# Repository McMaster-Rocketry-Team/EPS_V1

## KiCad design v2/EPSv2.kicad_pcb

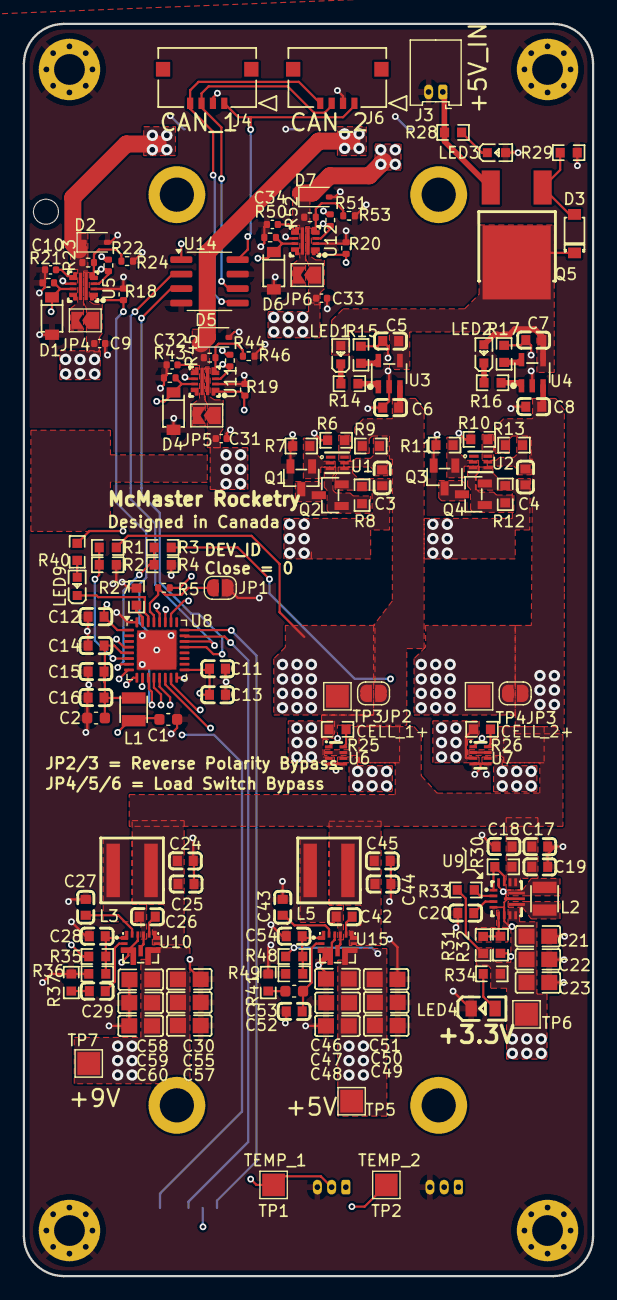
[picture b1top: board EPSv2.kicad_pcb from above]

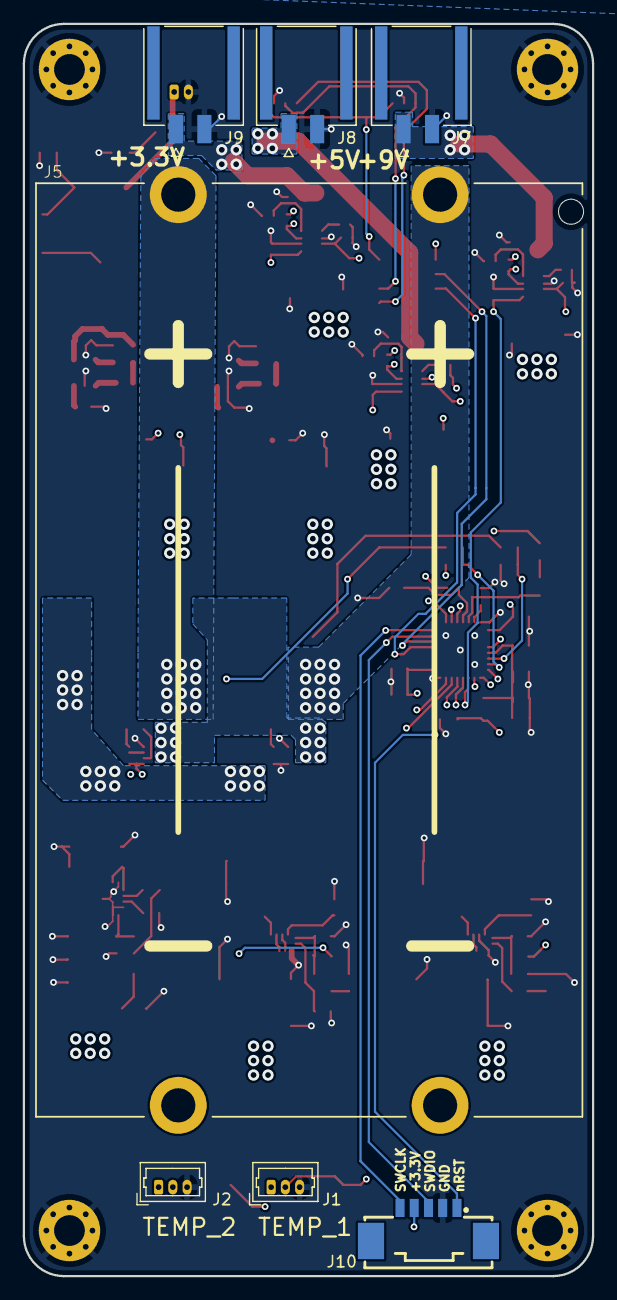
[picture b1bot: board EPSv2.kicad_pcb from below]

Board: 4 copper layers, 50.0 x 110.0 mm, 163 parts (7 on the bottom side), 85 nets.

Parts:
C1, C2: 47uF; C_0603_1608Metric
C3, C4, C12, C13, C15, C20: 100nF 0603; C0603
C5, C6, C7, C8, C11, C16: 4.7uF 0603; C0603
C9, C31, C33: 1u / 20V; C_0402_1005Metric
C10, C32, C34: 5n; C_0402_1005Metric
C14: 10nF 0603; C0603
C17, C18, C19: 10uF 0603; C0603
C21, C22, C23: 22uF 0805; C0805
C24, C45: CL10A106KP8NNNC (10uF 0603); C0603
C25, C26, C42, C44: CC0603KRX7R9BB104 (100nF 0603); C0603
C27, C43: CL10A225KO8NNNC; C0603
C28, C54: CL10C270JB8NNNC; C0603
C29: CC0603KRX7R9BB203; C0603
C30, C46, C47, C48, C49, C50, C51, C55, C57, C58, C59, C60: CL21A226MAQNNNE (22uF 0805); C0805
C52: CL10C220JB8NNNC; C0603
C53: 33nF; C_0603_1608Metric
D1, D4, D6: DDZ9678-7; SOD-123_L2.7-W1.6-LS3.7-RD
D2, D5, D7: 1N5819WS; D_SOD-323
D3: BZT52C11-7-F; SOD-123_L2.8-W1.8-LS3.7-RD
H1, H2, H3, H4: MountingHole_Pad; MountingHole_2.7mm_M2.5_Pad_Via
J1, J2: Conn_01x03; Molex_PicoBlade_53047-0310_1x03_P1.25mm_Vertical
J3: Conn_01x02; Molex_PicoBlade_53048-0210_1x02_P1.25mm_Horizontal
J4, J6: 5037630491; CON_5037630491
J5: 2P 21700 Cell Holder; PA21700x2-THM_Parallel
J7, J8, J9: 1053091102; 1054301102
J10: Conn_01x05_Pin; CONN-SMD_5P-P1.25_532610571-2
JP1, JP2, JP3: SolderJumper_2_Open; SolderJumper-2_P1.3mm_Open_RoundedPad1.0x1.5mm
JP4, JP5, JP6: SolderJumper_2_Open; SolderJumper-2_P1.3mm_Open_TrianglePad1.0x1.5mm
L1, L2: 1.5uF 2.9A; IND-SMD_L2.5-W2.0_MEKK2520TR47M
L3, L5: SRP5030CA-2R2M; IND-SMD_L5.5-W5.3
LED1, LED2, LED9: Yellow; LED0603-RD-YELLOW
LED3: KT-0603R (RED); LED0603-RD
LED4: 0805G (Green); LED0805-R-RD
Q1, Q2, Q3, Q4: AO3400A; SOT-23-3_L2.9-W1.3-P1.90-LS2.4-BR
Q5: AP25P06K; TO-252-2_L6.6-W6.1-P4.57-LS10.1-BL
R1, R2, R3, R4, R31: 470k 0603; R0603
R5: 10k; R_0402_1005Metric
R6, R10: 2.2k 0603; R0603
R7, R8, R11, R12: 2M 0603; R0603
R9, R13: 330R 0603; R0603
R14, R16, R28, R40: 0603WAF1001T5E (1k 0603); R0603
R15, R17: 2k 0603; R0603
R18, R19, R20: 470k; R_0402_1005Metric
R21, R22, R43, R44, R50, R51: 1k; R_0402_1005Metric
R23, R45, R52: 47k; R_0402_1005Metric
R24, R46, R53: 33k; R_0402_1005Metric
R25, R26, R33: 100k 0603; R0603
R27: 5.1k 0603; R0603
R29, R49: 0603WAF1003T5E (100k 0603); R0603
R30: 10k 0603; R0603
R32: 150k 0603; R0603
R34: 1k 0603; R0603
R35: FRC0603F1432TS; R0603
R36: 0603WAF2003T5E; R0603
R37: FRC0603F1872TS; R0603
R41: FRC0603F5761TS; R0603
R48: 0603WAF1372T5E; R0603
TP1, TP2, TP3, TP4, TP5, TP6, TP7: TestPoint; TestPoint_Pad_2.0x2.0mm
U1, U2: BQ29700DSER; WSON-6_L1.5-W1.5-P0.50-TL
U3, U4: MCP73831T-2ACI/OT; SOT-23-5_L3.0-W1.7-P0.95-LS2.8-BL
U5, U11, U12: LM73100RPWR; VQFN-10_L2.0-W2.0-P0.45-TL
U6, U7: C3235556 (M66200DRLR); SOT-583-8_L2.1-W1.2-P0.50-LS1.6-BL
U8: STM32L432KCUx; QFN-32-1EP_5x5mm_P0.5mm_EP3.45x3.45mm
U9: TPS63070RNMR; VQFN-HR-15_L3.0-W2.5-P0.50-BL_TPS63070RNMR
U10, U15: TPS61288LRQQR; VQFN-HR-11_L3.0-W2.5-P0.50-TL
U14: ISO1044BD; SOIC-8_3.9x4.9mm_P1.27mm

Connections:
+3.3V: C1.1, C11.2, C12.2, C13.2, C21.2, C22.2, C23.2, C33.1, J1.1, J2.1, J10.4, JP6.1 (A), L1.1, R5.1, R22.1, R31.2, R33.2, R34.2, R40.2, R44.1, R51.1, TP6.1, U8.1 (VDD), U8.17 (VDD), U9.7 (Vout), U9.8 (Vout), U12.5 (IN)
+3.3V_PG: R51.2, U8.26 (PB3), U12.3 (PG)
+5V: C31.1, C46.2, C47.2, C48.2, C49.2, C50.2, C51.2, JP5.1 (A), R48.2, TP5.1, U11.5 (IN), U15.5 (VOUT)
+5V_PG: R44.2, U8.27 (PB4), U11.3 (PG)
+9V: C9.1, C30.2, C55.2, C57.2, C58.2, C59.2, C60.2, JP4.1 (A), R35.2, TP7.1, U5.5 (IN), U10.5 (VOUT)
+9V_PG: R22.2, U5.3 (PG), U8.28 (PB5)
/DEV_ID: JP1.1 (A), R5.2, U8.29 (PB6)
/LM7310_3.3V/VOUT: D7.1 (K), J9.1, JP6.2 (B), R52.1, U12.6 (OUT)
/LM7310_5V/VOUT: D5.1 (K), J8.1, JP5.2 (B), R45.1, U11.6 (OUT)
/LM7310_9V/VOUT: D2.1 (K), J7.1, JP4.2 (B), R23.1, U5.6 (OUT)
/LM66200_2/VOUT: C17.2, C18.2, C19.2, C24.2, C25.2, C44.2, C45.2, L3.1, L5.1, R30.2, U6.2 (VOUT), U6.7 (VOUT), U7.2 (VOUT), U7.7 (VOUT), U9.12 (Vin), U9.13 (Vin), U10.6 (EN), U10.7 (VIN), U15.6 (EN), U15.7 (VIN)
/MCP73831_1/+5V_VIN: C5.2, C7.2, D3.1 (K), LED1.2 (A), LED2.2 (A), Q5.3 (D), U3.4 (VDD), U4.4 (VDD)
/Reverse_Polarity/VIN: J3.1, Q5.2 (S), R28.2
/STM32L432KCUx/+3V3A: C2.1, C14.2, C15.2, C16.2, L1.2, U8.5 (VDDA)
/STM32L432KCUx/PB7: LED9.1 (C), U8.30 (PB7)
/STM32L432KCUx/SWDCLK: J10.5, U8.24 (PA14)
/STM32L432KCUx/SWDIO: J10.3, U8.23 (PA13)
/STM32L432KCUx/nRST: J10.1, U8.4 (NRST)
CAN_RX: U8.21 (PA11), U14.3 (RXD)
CAN_TX: U8.22 (PA12), U14.2 (TXD)
CELL_1+: C6.2, J5.4, JP2.1 (A), JP2.2 (B), R1.2, R9.2, R25.2, R26.2, TP3.1, U3.3 (VBAT), U6.3 (VIN1), U7.3 (VIN1)
CELL_1-: C3.1, J5.3, Q2.2 (S), R8.1, U1.4 (VSS)
CELL_1_VMON: R1.1, R2.2, U8.6 (PA0)
CELL_2+: C8.2, J5.1, JP3.1 (A), JP3.2 (B), R3.2, R13.2, TP4.1, U4.3 (VBAT), U6.6 (VIN2), U7.6 (VIN2)
CELL_2-: C4.1, J5.2, Q4.2 (S), R12.1, U2.4 (VSS)
CELL_2_VMON: R3.1, R4.2, U8.7 (PA1)
GND: C1.2, C2.2, C5.1, C6.1, C7.1, C8.1, C9.2, C10.2, C11.1, C12.1, C13.1, C14.1, C15.1, C16.1, C17.1, C18.1, C19.1, C20.1, C21.1, C22.1, C23.1, C24.1, C25.1, C27.1, C28.1, C30.1, C31.2, C32.2, C33.2, C34.2, C43.1, C44.1, C45.1, C46.1, C47.1, C48.1, C49.1, C50.1, C51.1, C52.1, C54.1, C55.1, C57.1, C58.1, C59.1, C60.1, D1.2 (A), D2.2 (A), D4.2 (A), D5.2 (A), D6.2 (A), D7.2 (A), H1.1, H2.1, H3.1, H4.1, J1.3, J2.3, J3.2, J4.2 (GND), J6.2 (GND), J7.2, J8.2, J9.2, J10.2, JP1.2 (B), LED3.2 (A), LED4.2 (K), Q1.2 (S), Q3.2 (S), R2.1, R4.1, R6.1, R7.1, R10.1, R11.1, R15.1, R17.1, R18.2, R19.2, R20.2, R21.2, R24.2, R27.1, R29.1, R32.1, R36.1, R37.1, R41.1, R43.2, R46.2, R49.1, R50.2, R53.2, U3.2 (VSS), U4.2 (VSS), U5.2 (OVLO), U5.8 (GND), U6.1 (GND), U6.4 (~ON), U6.5 (GND), U7.1 (GND), U7.4 (~ON), U7.5 (GND), U8.16 (VSS), U8.32 (VSS), U8.33 (VSS), U9.4 (GND), U9.6 (FB2), U9.10 (PGND), U9.15 (Vsel), U10.3 (PGND), U10.10 (AGND), U11.2 (OVLO), U11.8 (GND), U12.2 (OVLO), U12.8 (GND), U14.4 (GND1), U14.7 (GND2), U15.3 (PGND), U15.10 (AGND)
LM7310_IOUT_1: D1.1 (C), R21.1, U5.9 (IMON), U8.8 (PA2)
LM7310_IOUT_2: D4.1 (C), R43.1, U8.9 (PA3), U11.9 (IMON)
LM7310_IOUT_3: D6.1 (C), R50.1, U8.10 (PA4), U12.9 (IMON)
unnamed: C26.2, L3.2, U10.4 (SW), U10.9 (SW)
unnamed: C29.1, R37.2
unnamed: C42.2, L5.2, U15.4 (SW), U15.9 (SW)
unnamed: C53.2, R41.2
unnamed: D3.2 (A), Q5.1 (G), R29.2
unnamed: J4.3 (CANH), J6.3 (CANH), U14.6 (CANH)
unnamed: J4.4 (CANL), J6.4 (CANL), U14.5 (CANL)
unnamed: J4.1 (VCC), J6.1 (VCC), U14.1 (VCC1), U14.8 (VCC2)
unnamed: LED1.1 (C), R14.1
unnamed: LED2.1 (C), R16.1
unnamed: LED3.1 (K), R28.1
unnamed: LED4.1 (A), R34.1
unnamed: LED9.2 (A), R40.1
unnamed: Q1.3 (D), Q2.3 (D)
unnamed: Q1.1 (G), R7.2, U1.2 (COUT)
unnamed: Q2.1 (G), R8.2, U1.3 (DOUT)
unnamed: Q3.3 (D), Q4.3 (D)
unnamed: Q3.1 (G), R11.2, U2.2 (COUT)
unnamed: Q4.1 (G), R12.2, U2.3 (DOUT)
unnamed: C3.2, R9.1, U1.5 (BAT)
unnamed: R6.2, U1.6 (V-)
unnamed: C4.2, R13.1, U2.5 (BAT)
unnamed: R10.2, U2.6 (V-)
unnamed: R15.2, U3.5 (PROG)
unnamed: R14.2, U3.1 (STAT)
unnamed: R17.2, U4.5 (PROG)
unnamed: R16.2, U4.1 (STAT)
unnamed: C10.1, U5.7 (DVDT)
unnamed: R23.2, R24.1, U5.4 (PGTH)
unnamed: R25.1, U6.8 (ST)
unnamed: R26.1, U7.8 (ST)
unnamed: R27.2, U8.31 (PH3)
unnamed: R30.1, U9.1 (PS/SYNC), U9.14 (EN)
unnamed: R31.1, R32.2, U9.5 (FB)
unnamed: L2.1, U9.11 (L1)
unnamed: L2.2, U9.9 (L2)
unnamed: R33.1, U9.2 (PG)
unnamed: C20.2, U9.3 (Vaux)
unnamed: C26.1, U10.8 (BST)
unnamed: C29.2, U10.2 (COMP)
unnamed: C28.2, R35.1, R36.2, U10.1 (FB)
unnamed: C27.2, U10.11 (VCC)
unnamed: C32.1, U11.7 (DVDT)
unnamed: R45.2, R46.1, U11.4 (PGTH)
unnamed: C34.1, U12.7 (DVDT)
unnamed: R52.2, R53.1, U12.4 (PGTH)
unnamed: C42.1, U15.8 (BST)
unnamed: C52.2, C53.1, U15.2 (COMP)
unnamed: C54.2, R48.1, R49.2, U15.1 (FB)
unnamed: C43.2, U15.11 (VCC)
TEMP_1: J1.2, TP1.1, U8.14 (PB0)
TEMP_2: J2.2, TP2.1, U8.15 (PB1)
~MCU_LS_1: R18.1, U5.1 (EN/UVLO), U8.11 (PA5)
~MCU_LS_2: R19.1, U8.12 (PA6), U11.1 (EN/UVLO)
~MCU_LS_3: R20.1, U8.13 (PA7), U12.1 (EN/UVLO)

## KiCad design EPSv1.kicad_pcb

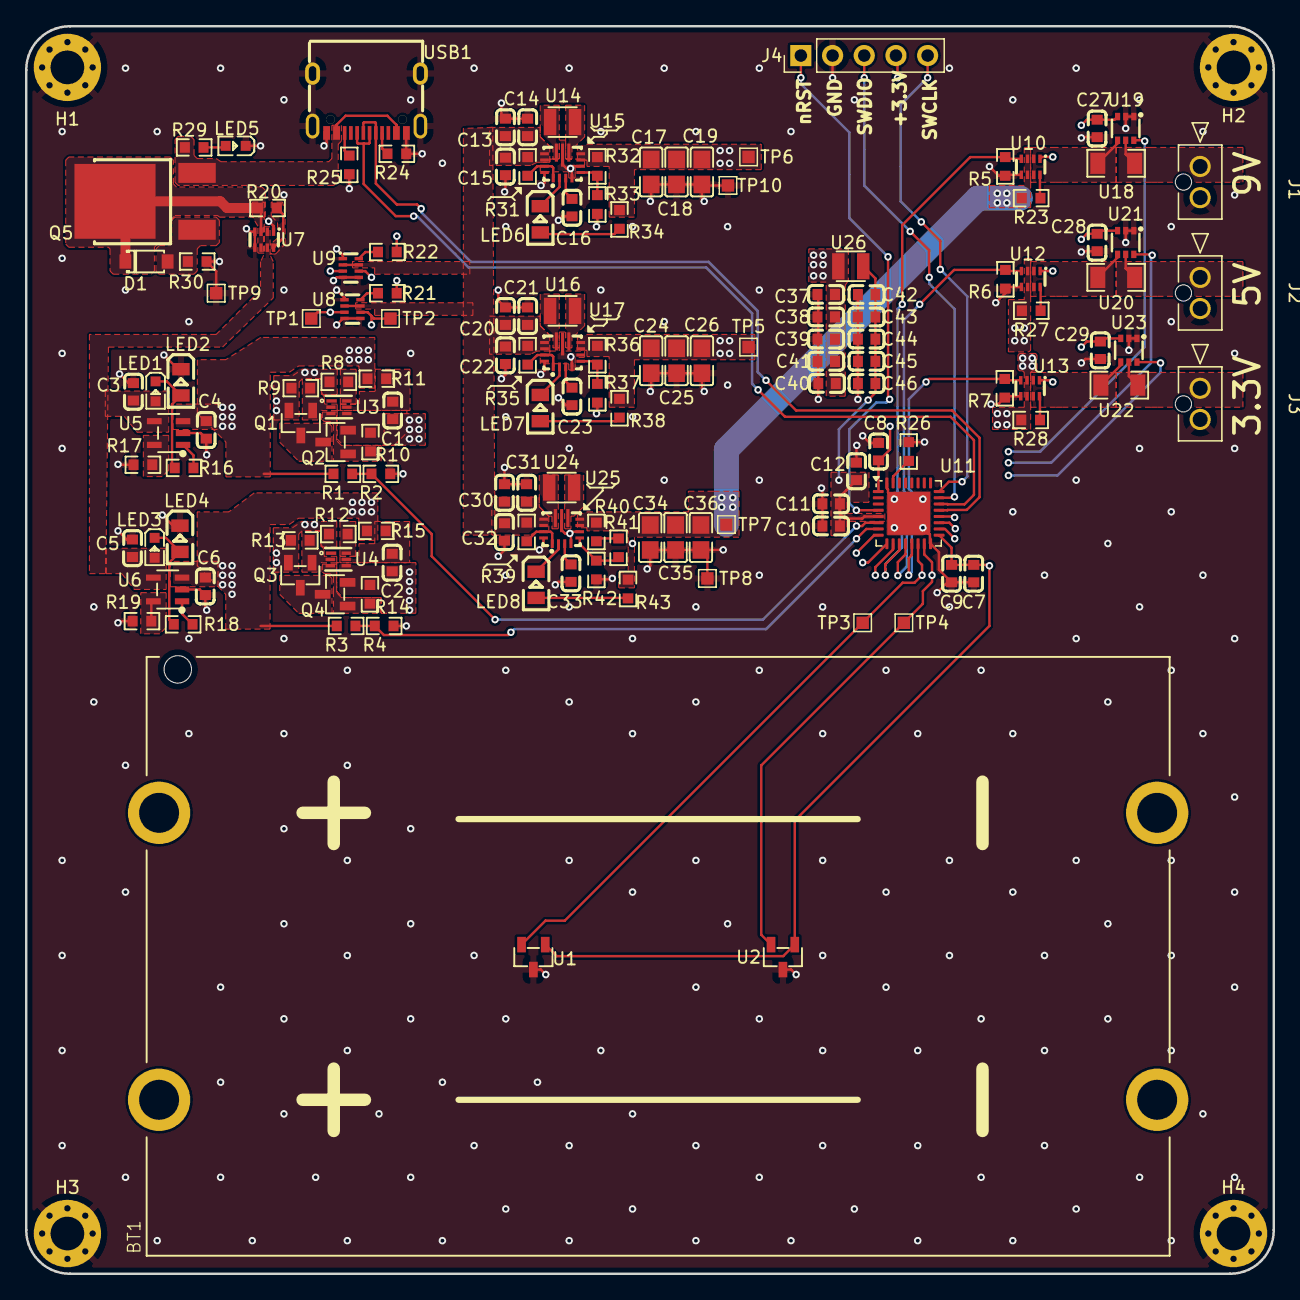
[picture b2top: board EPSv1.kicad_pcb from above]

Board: 4 copper layers, 100.0 x 100.0 mm, 149 parts (0 on the bottom side), 83 nets.

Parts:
BT1: 2P 21700 Cell Holder; PA21700x2-THM_Parallel
C1, C2, C8, C9, C11, C16, C23, C27, C28, C29, C33: 100nF 0603; C0603
C3, C4, C5, C6, C7, C12: 4.7uF 0603; C0603
C10: 10nF 0603; C0603
C13, C14, C15, C20, C21, C22, C30, C31, C32, C37, C38, C39, C40, C41, C42, C43, C44, C45, C46: 10uF 0603; C0603
C17, C18, C19, C24, C25, C26, C34, C35, C36: 22uF 0805; C0805
D1: BZT52C11-7-F; SOD-123_L2.8-W1.8-LS3.7-RD
H1, H2, H3, H4: MountingHole_Pad; MountingHole_2.7mm_M2.5_Pad_Via
J1, J2, J3: 1053091102; CON_1053091102
J4: Conn_01x05_Pin; PinHeader_1x05_P2.54mm_Vertical
LED1, LED3: Yellow; LED0603-RD-YELLOW
LED2, LED4: Green; LED0805-R-RD
LED5: KT-0603R (RED); LED0603-RD
LED6, LED7, LED8: 0805G (Green); LED0805-R-RD
Q1, Q2, Q3, Q4: AO3400A; SOT-23-3_L2.9-W1.3-P1.90-LS2.4-BR
Q5: AP25P06K; TO-252-2_L6.6-W6.1-P4.57-LS10.1-BL
R1, R2, R3, R4, R32: 470k 0603; R0603
R5, R6, R7, R20, R21, R22, R23, R27, R28: 100k 0603; R0603
R8, R12: 2.2k 0603; R0603
R9, R10, R13, R14: 2M 0603; R0603
R11, R15, R16, R18, R34, R38, R43: 330R 0603; R0603
R17, R19: 2k 0603; R0603
R24, R25, R26: 5.1k 0603; R0603
R29: 0603WAF1001T5E (1k 0603); R0603
R30: 0603WAF1003T5E (100k 0603); R0603
R31, R35, R39: 10k 0603; R0603
R33: 150k 0603; R0603
R36: 680k 0603; R0603
R37: 130k 0603; R0603
R40: 300k 0603; R0603
R41, R42: 33k 0603; R0603
TP1, TP2, TP3, TP4, TP5, TP6, TP7, TP8, TP9, TP10: TestPoint; TestPoint_Pad_1.0x1.0mm
U1, U2: MCP9700AT-E/TT; SOT-23-3_L2.9-W1.3-P1.90-LS2.4-BR
U3, U4: BQ29700DSER; WSON-6_L1.5-W1.5-P0.50-TL
U5, U6: MCP73831T-2ACI/OT; SOT-23-5_L3.0-W1.7-P0.95-LS2.8-BL
U7, U8, U9, U10, U12, U13: C3235556 (M66200DRLR); SOT-583-8_L2.1-W1.2-P0.50-LS1.6-BL
U11: STM32L432KCUx; QFN-32-1EP_5x5mm_P0.5mm_EP3.45x3.45mm
U14, U16, U24, U26: 1.5uF 2.9A; IND-SMD_L2.5-W2.0_MEKK2520TR47M
U15, U17, U25: TPS63070RNMR; VQFN-HR-15_L3.0-W2.5-P0.50-BL_TPS63070RNMR
U18, U20, U22: 20m 1206; R1206
U19, U21, U23: INA199A1DCKR; SC-70-6_L2.2-W1.3-P0.65-LS2.1-BR
USB1: TYPE-C 16PIN 2MD(073); USB-C-SMD_TYPE-C-6PIN-2MD-073

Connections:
+3.3V: C7.2, C8.2, C9.2, C17.2, C18.2, C19.2, C27.2, C28.2, C29.2, C37.2, C38.2, C39.2, C40.2, C41.2, J4.4, R28.2, R32.2, R34.2, TP6.1, U1.1 (VDD), U2.1 (VDD), U11.1 (VDD), U11.17 (VDD), U13.3 (VIN1), U13.6 (VIN2), U15.7 (Vout), U15.8 (Vout), U19.3 (V+), U21.3 (V+), U23.3 (V+), U26.1
+5V: C24.2, C25.2, C26.2, R27.2, R36.2, R38.2, TP5.1, U12.3 (VIN1), U12.6 (VIN2), U17.7 (Vout), U17.8 (Vout)
+9V: C34.2, C35.2, C36.2, R23.2, R40.2, R43.2, TP7.1, U10.3 (VIN1), U10.6 (VIN2), U25.7 (Vout), U25.8 (Vout)
/INA199_1/IN+: U10.2 (VOUT), U10.7 (VOUT), U18.1, U19.4 (IN+)
/INA199_1/IN-: J1.1, U18.2, U19.5 (IN-)
/INA199_2/IN+: U12.2 (VOUT), U12.7 (VOUT), U20.1, U21.4 (IN+)
/INA199_2/IN-: J2.1, U20.2, U21.5 (IN-)
/INA199_3/IN+: U13.2 (VOUT), U13.7 (VOUT), U22.1, U23.4 (IN+)
/INA199_3/IN-: J3.1, U22.2, U23.5 (IN-)
/LM66200_1/VIN1: D1.1 (K), Q5.3 (D), R20.2, U7.3 (VIN1), U7.6 (VIN2)
/LM66200_1/VOUT: C3.2, C5.2, LED1.2 (A), LED3.2 (A), U5.4 (VDD), U6.4 (VDD), U7.2 (VOUT), U7.7 (VOUT)
/LM66200_2/VOUT: C13.2, C14.2, C15.2, C20.2, C21.2, C22.2, C30.2, C31.2, C32.2, R31.2, R35.2, R39.2, U8.2 (VOUT), U8.7 (VOUT), U9.2 (VOUT), U9.7 (VOUT), U15.12 (Vin), U15.13 (Vin), U17.12 (Vin), U17.13 (Vin), U25.12 (Vin), U25.13 (Vin)
/STM32L432KCUx/+3V3A: C10.2, C11.2, C12.2, C42.2, C43.2, C44.2, C45.2, C46.2, U11.5 (VDDA), U26.2
/STM32L432KCUx/DN: U11.21 (PA11), USB1.5 (DN2), USB1.7 (DN1)
/STM32L432KCUx/DP: U11.22 (PA12), USB1.6 (DP1), USB1.8 (DP2)
/STM32L432KCUx/SWDCLK: J4.5, U11.24 (PA14)
/STM32L432KCUx/SWDIO: J4.3, U11.23 (PA13)
/STM32L432KCUx/nRST: J4.1, U11.4 (NRST)
CELL_1+: BT1.4, C4.2, R1.2, R11.2, R21.2, R22.2, TP1.1, U5.3 (VBAT), U8.3 (VIN1), U9.3 (VIN1)
CELL_1-: BT1.3, C1.1, Q2.2 (S), R10.1, U3.4 (VSS)
CELL_2+: BT1.1, C6.2, R3.2, R15.2, TP2.1, U6.3 (VBAT), U8.6 (VIN2), U9.6 (VIN2)
CELL_2-: BT1.2, C2.1, Q4.2 (S), R14.1, U4.4 (VSS)
GND: C3.1, C4.1, C5.1, C6.1, C7.1, C8.1, C9.1, C10.1, C11.1, C12.1, C13.1, C14.1, C15.1, C16.1, C17.1, C18.1, C19.1, C20.1, C21.1, C22.1, C23.1, C24.1, C25.1, C26.1, C27.1, C28.1, C29.1, C30.1, C31.1, C32.1, C33.1, C34.1, C35.1, C36.1, C37.1, C38.1, C39.1, C40.1, C41.1, C42.1, C43.1, C44.1, C45.1, C46.1, H1.1, H2.1, H3.1, H4.1, J1.2, J2.2, J3.2, J4.2, LED2.2 (K), LED4.2 (K), LED5.1 (K), Q1.2 (S), Q3.2 (S), R2.1, R4.1, R5.1, R6.1, R7.1, R8.1, R9.1, R12.1, R13.1, R17.1, R19.1, R24.2, R25.2, R26.1, R30.1, R33.1, R37.1, R42.1, TP8.1, TP9.1, TP10.1, U1.3 (GND), U2.3 (GND), U5.2 (VSS), U6.2 (VSS), U7.1 (GND), U7.4 (~ON), U7.5 (GND), U8.1 (GND), U8.4 (~ON), U8.5 (GND), U9.1 (GND), U9.4 (~ON), U9.5 (GND), U10.1 (GND), U10.5 (GND), U11.16 (VSS), U11.32 (VSS), U11.33 (VSS), U12.1 (GND), U12.5 (GND), U13.1 (GND), U13.5 (GND), U15.4 (GND), U15.6 (FB2), U15.10 (PGND), U15.15 (Vsel), U17.4 (GND), U17.6 (FB2), U17.10 (PGND), U17.15 (Vsel), U19.1 (REF), U19.2 (GND), U21.1 (REF), U21.2 (GND), U23.1 (REF), U23.2 (GND), U25.4 (GND), U25.6 (FB2), U25.10 (PGND), U25.15 (Vsel), USB1.1 (GND), USB1.12 (GND), USB1.13 (SHELL), USB1.14 (SHELL)
INA199_1: U11.8 (PA2), U19.6 (OUT)
INA199_2: U11.9 (PA3), U21.6 (OUT)
INA199_3: U11.10 (PA4), U23.6 (OUT)
unnamed: D1.2 (A), Q5.1 (G), R30.2
unnamed: LED1.1 (C), LED2.1 (A), R16.1
unnamed: LED3.1 (C), LED4.1 (A), R18.1
unnamed: LED5.2 (A), R29.1
unnamed: LED6.1 (A), R34.1
unnamed: LED6.2 (K), U15.2 (PG)
unnamed: LED7.1 (A), R38.1
unnamed: LED7.2 (K), U17.2 (PG)
unnamed: LED8.1 (A), R43.1
unnamed: LED8.2 (K), U25.2 (PG)
unnamed: Q1.3 (D), Q2.3 (D)
unnamed: Q1.1 (G), R9.2, U3.2 (COUT)
unnamed: Q2.1 (G), R10.2, U3.3 (DOUT)
unnamed: Q3.3 (D), Q4.3 (D)
unnamed: Q3.1 (G), R13.2, U4.2 (COUT)
unnamed: Q4.1 (G), R14.2, U4.3 (DOUT)
unnamed: R40.1, R41.2
unnamed: C1.2, R11.1, U3.5 (BAT)
unnamed: R8.2, U3.6 (V-)
unnamed: C2.2, R15.1, U4.5 (BAT)
unnamed: R12.2, U4.6 (V-)
unnamed: R17.2, U5.5 (PROG)
unnamed: R16.2, U5.1 (STAT)
unnamed: R19.2, U6.5 (PROG)
unnamed: R18.2, U6.1 (STAT)
unnamed: R20.1, U7.8 (ST)
unnamed: R21.1, U8.8 (ST)
unnamed: R22.1, U9.8 (ST)
unnamed: R23.1, U10.8 (ST)
unnamed: R26.2, U11.31 (PH3)
unnamed: R27.1, U12.8 (ST)
unnamed: R28.1, U13.8 (ST)
unnamed: R31.1, U15.1 (PS/SYNC), U15.14 (EN)
unnamed: R32.1, R33.2, U15.5 (FB)
unnamed: U14.1, U15.11 (L1)
unnamed: U14.2, U15.9 (L2)
unnamed: C16.2, U15.3 (Vaux)
unnamed: R35.1, U17.1 (PS/SYNC), U17.14 (EN)
unnamed: R36.1, R37.2, U17.5 (FB)
unnamed: U16.1, U17.11 (L1)
unnamed: U16.2, U17.9 (L2)
unnamed: C23.2, U17.3 (Vaux)
unnamed: R39.1, U25.1 (PS/SYNC), U25.14 (EN)
unnamed: R41.1, R42.2, U25.5 (FB)
unnamed: U24.1, U25.11 (L1)
unnamed: U24.2, U25.9 (L2)
unnamed: C33.2, U25.3 (Vaux)
unnamed: R24.1, USB1.4 (CC1)
unnamed: R25.1, USB1.10 (CC2)
PA0: R1.1, R2.2, U11.6 (PA0)
PA1: R3.1, R4.2, U11.7 (PA1)
PB0: TP3.1, U1.2 (VOUT), U11.14 (PB0)
PB1: TP4.1, U2.2 (VOUT), U11.15 (PB1)
USB_+5V: Q5.2 (S), R29.2, USB1.2 (VBUS), USB1.11 (VBUS)
~MCU_LS_1: R5.2, U10.4 (~ON), U11.11 (PA5)
~MCU_LS_2: R6.2, U11.12 (PA6), U12.4 (~ON)
~MCU_LS_3: R7.2, U11.13 (PA7), U13.4 (~ON)

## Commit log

2024-10-05 started block layout
2024-10-06 added molex nanofit
2024-10-10 Laid out all the blocks and imported the board outline
2024-10-13 100x100 board size
2024-10-14 adde new blocks
2024-10-21 exported STEP
2024-10-27 started proper layout
2024-11-11 v0.1 sent to JLCPCB
2024-11-25 added documentation folder
2024-12-02 updated documentation
2024-12-06 testing
2025-02-16 layout started
2025-02-17 preliminary layout
2025-02-17 battery charging routing
2025-02-22 routing done
2025-02-23 CAN txrx
2025-03-03 can transceiver and battery reverse polarity bypass
2025-03-04 load switch default OFF
2025-03-04 cleared unrouted
2025-03-05 minor changes for silkscreen
2025-05-24 Component selection nearly complete
2025-05-24 finished component selection
2025-05-25 bigger current ratings for 5V and 9V
